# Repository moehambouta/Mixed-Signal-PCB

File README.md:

# Mixed Signal PCB Project

This repository contains all the source files for the Mixed Signal PCB Project, an endeavor to design and develop a PCB capable of signal generation and analysis within the audio band. The project is thoroughly documented through a series of blog posts available at [Mixed Signal PCB Project Blog](https://www.mohamedhambouta.com/article/36e01b97-5775-4c1d-bf0c-83d208441204).

## Repository Structure

- `Assembly` - Contains the bill of materials and assembly information.
- `Components` - Individual component files used in the design.
- `Gerber` - Gerber files necessary for PCB manufacturing.
- `Media` - Images and videos showcasing the PCB and its design process.
- `PCB` - The KiCAD PCB design file.
- `Schematics` - Schematic files for each section of the PCB design.

## Acknowledgments

Special thanks to Phil's Lab for their course, which significantly contributed to the knowledge and techniques applied in this project. Find the course details [here](https://phils-lab-shop.fedevel.education/itemDetail.html?itemtype=course&dbid=1606477016678&instrid=us-east-2_Vw1KnTvTs:107c257d-31cc-430a-95d7-3c5d70c578e0).

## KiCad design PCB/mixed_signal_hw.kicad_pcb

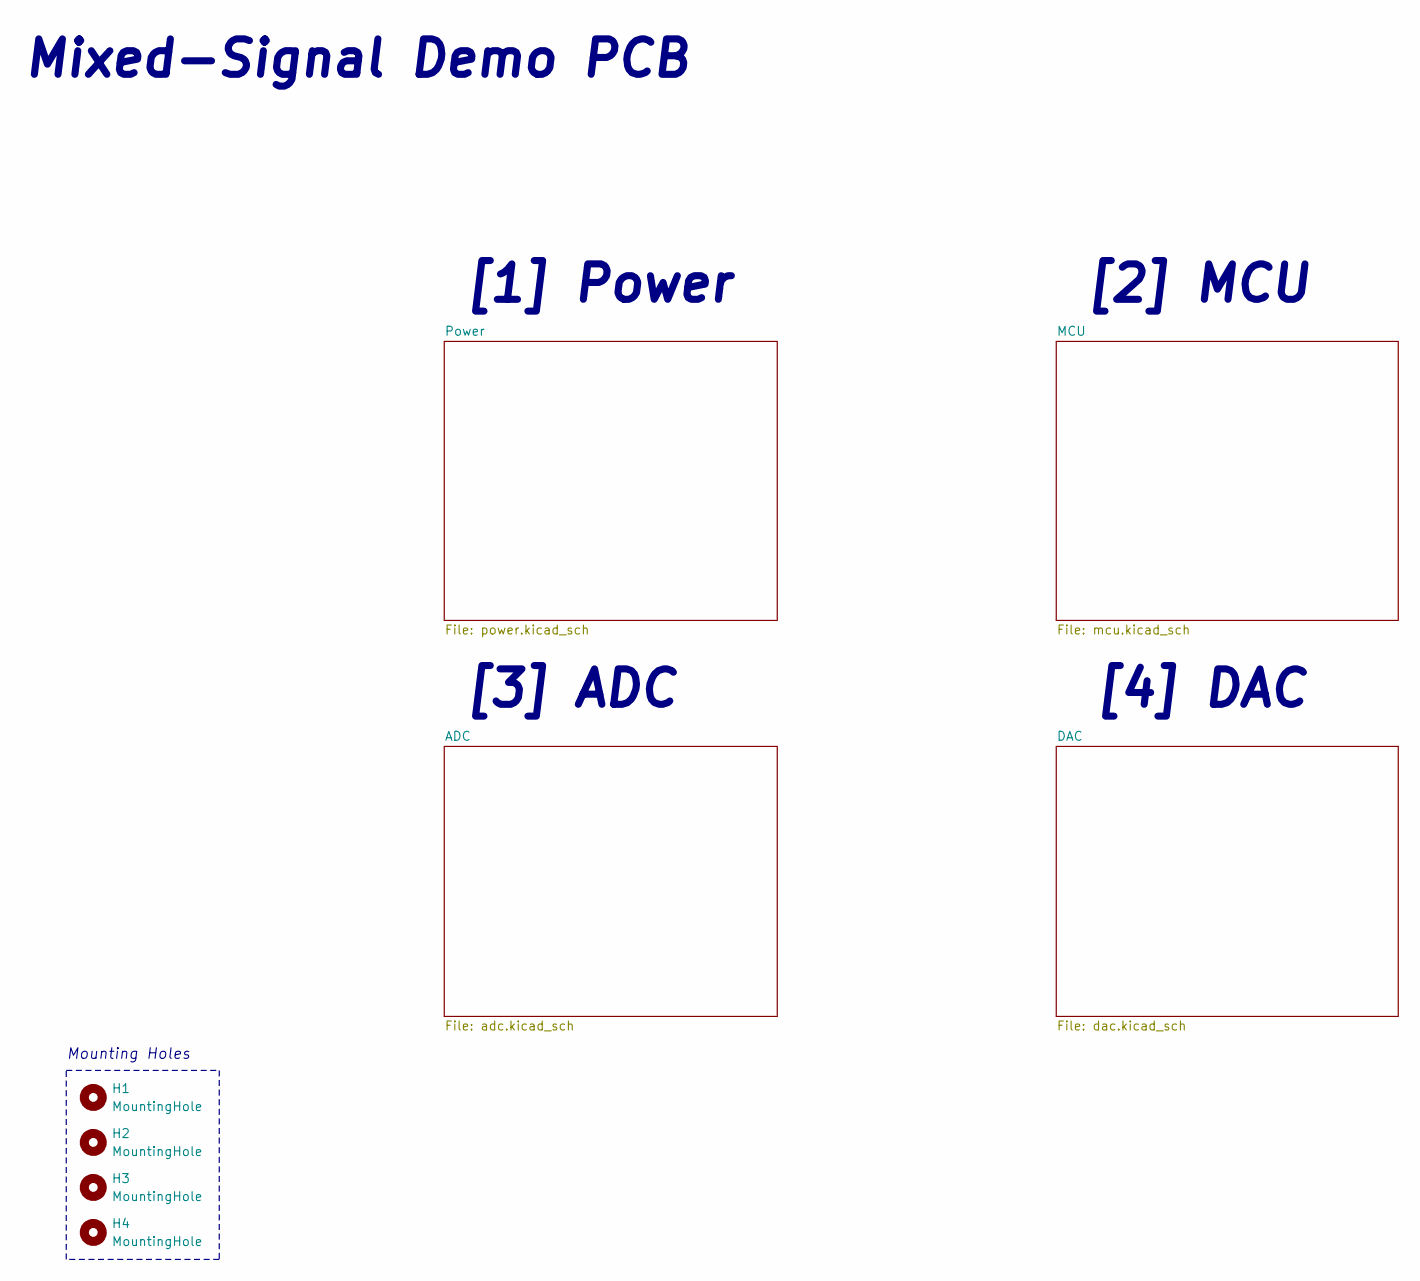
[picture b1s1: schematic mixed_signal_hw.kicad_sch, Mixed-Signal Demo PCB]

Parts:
H1, H2, H3, H4: MountingHole; MountingHole_3.2mm_M3

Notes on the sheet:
Mounting Holes
[4] DAC
[1] Power
[3] ADC
[2] MCU
Mixed-Signal Demo PCB

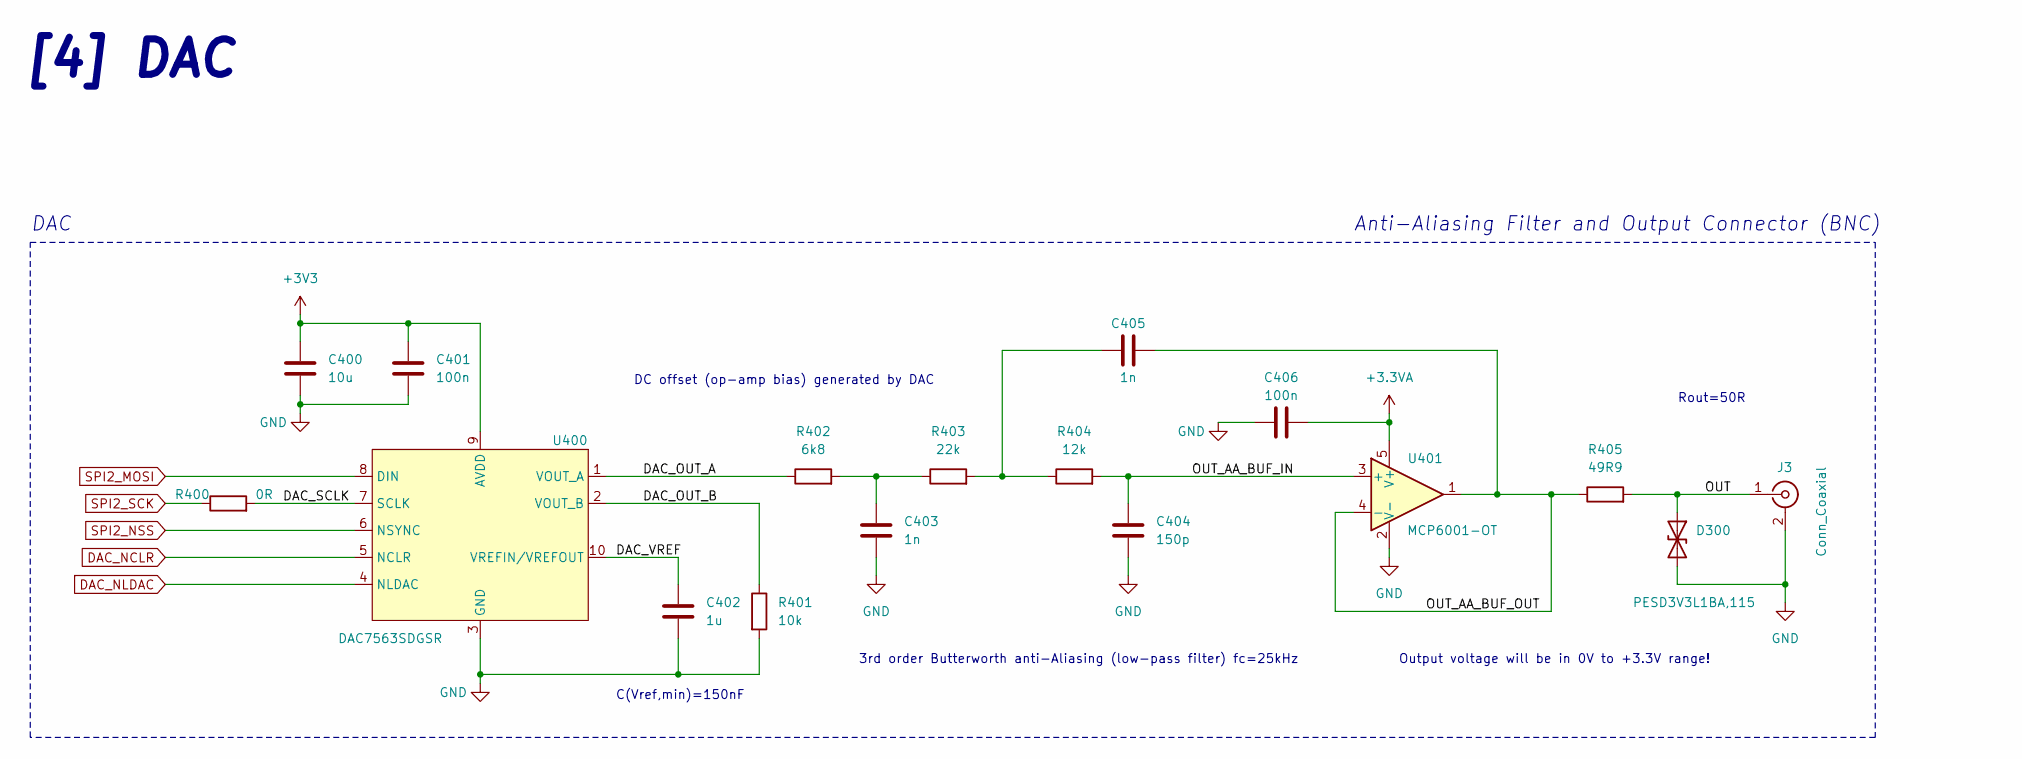
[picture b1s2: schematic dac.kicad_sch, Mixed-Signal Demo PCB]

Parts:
C400: 10u; C_0603_1608Metric
C401, C406: 100n; C_0402_1005Metric
C402: 1u; C_0603_1608Metric
C403, C405: 1n; C_0402_1005Metric
C404: 150p; C_0402_1005Metric
D300: PESD3V3L1BA,115; D_SOD-323
J3: Conn_Coaxial; AMPHENOL-BNC-031-5640-1010
R400: 0R; R_0402_1005Metric
R401: 10k; R_0402_1005Metric
R402: 6k8; R_0402_1005Metric
R403: 22k; R_0402_1005Metric
R404: 12k; R_0402_1005Metric
R405: 49R9; R_0402_1005Metric
U400: DAC7563SDGSR; VSSOP-10
U401: MCP6001-OT; SOT-23-5

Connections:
+3.3VA: C406.2, U401.5 (V+); also elsewhere on the board
+3V3: C400.1, C401.1, U400.9 (AVDD); also elsewhere on the board
/DAC/DAC_OUT_A: R402.1, U400.1 (VOUT_A)
/DAC/DAC_OUT_B: R401.1, U400.2 (VOUT_B)
/DAC/DAC_SCLK: R400.2, U400.7 (SCLK)
/DAC/DAC_VREF: C402.1, U400.10 (VREFIN/VREFOUT)
/DAC/OUT_AA_BUF_IN: C404.1, R404.2, U401.3 (+)
/DAC/OUT_AA_BUF_OUT: C405.2, R405.1, U401.1, U401.4 (-)
DAC_NCLR: U400.5 (NCLR); also elsewhere on the board
DAC_NLDAC: U400.4 (NLDAC); also elsewhere on the board
unnamed: C403.1, R402.2, R403.1
unnamed: C405.1, R403.2, R404.1
SPI2_MOSI: U400.8 (DIN); also elsewhere on the board
SPI2_NSS: U400.6 (NSYNC); also elsewhere on the board
SPI2_SCK: R400.1; also elsewhere on the board

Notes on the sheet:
Output voltage will be in 0V to +3.3V range!
Anti-Aliasing Filter and Output Connector (BNC)
3rd order Butterworth anti-Aliasing (low-pass filter) fc=25kHz
DAC
C(Vref,min)=150nF
DC offset (op-amp bias) generated by DAC
[4] DAC
Rout=50R

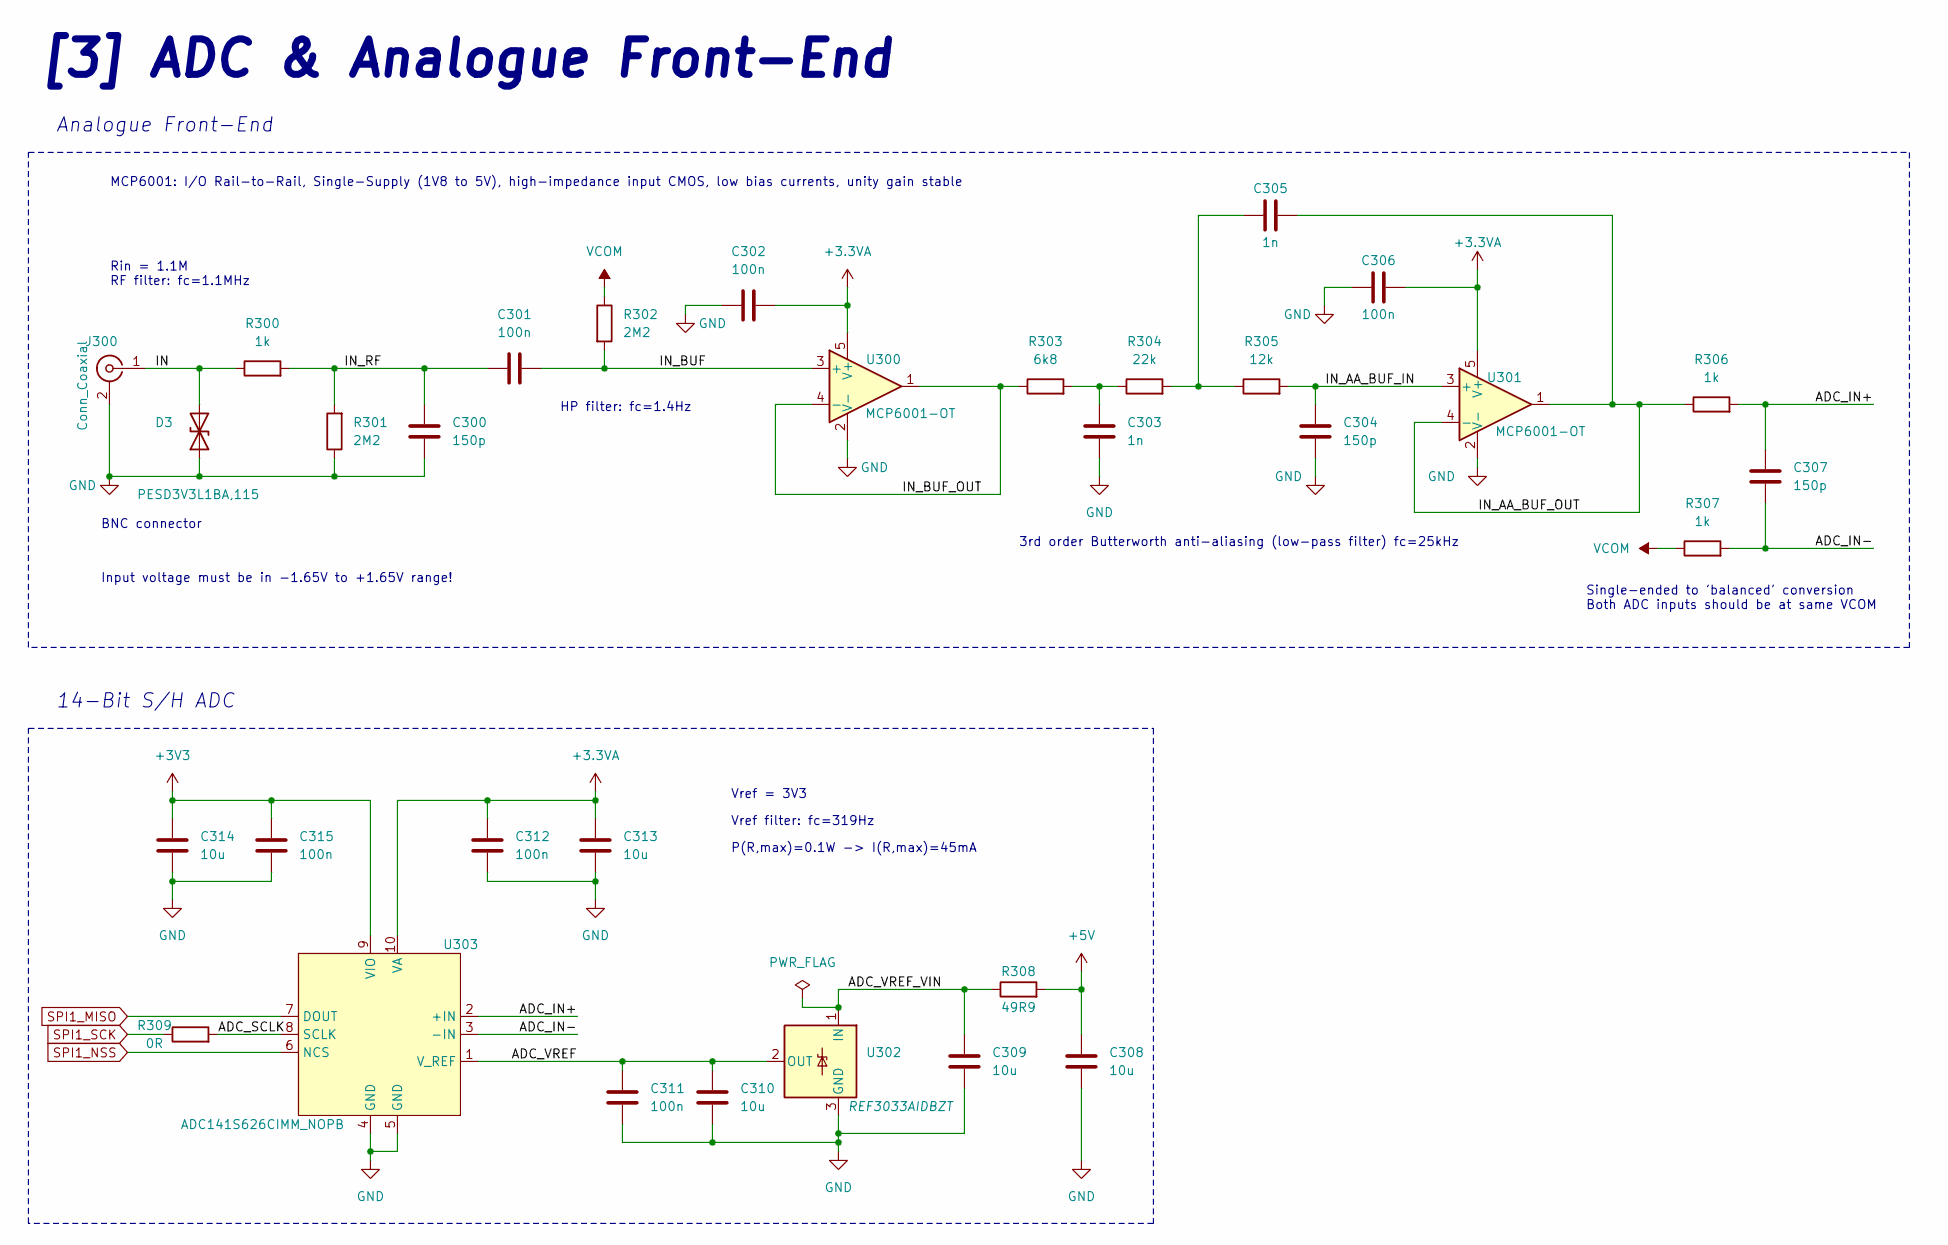
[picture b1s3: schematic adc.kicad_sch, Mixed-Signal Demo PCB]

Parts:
C300, C304, C307: 150p; C_0402_1005Metric
C301, C302, C306, C312, C315: 100n; C_0402_1005Metric
C303, C305: 1n; C_0402_1005Metric
C308, C309, C313, C314: 10u; C_0603_1608Metric
C310: 10u; C_0402_1005Metric
C311: 100n; C_0603_1608Metric
D3: PESD3V3L1BA,115; D_SOD-323
J300: Conn_Coaxial; AMPHENOL-BNC-031-5640-1010
R300, R306, R307: 1k; R_0402_1005Metric
R301, R302: 2M2; R_0402_1005Metric
R303: 6k8; R_0402_1005Metric
R304: 22k; R_0402_1005Metric
R305: 12k; R_0402_1005Metric
R308: 49R9; R_0402_1005Metric
R309: 0R; R_0402_1005Metric
U300, U301: MCP6001-OT; SOT-23-5
U302: REF3033AIDBZT; SOT-23
U303: ADC141S626CIMM_NOPB; VSSOP-10

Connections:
+3.3VA: C302.2, C306.1, C312.1, C313.1, U300.5 (V+), U301.5 (V+), U303.10 (VA); also elsewhere on the board
+3V3: C314.1, C315.1, U303.9 (VIO); also elsewhere on the board
+5V: C308.1, R308.2; also elsewhere on the board
/ADC/ADC_IN+: C307.1, R306.2, U303.2 (+IN)
/ADC/ADC_IN-: C307.2, R307.2, U303.3 (-IN)
/ADC/ADC_SCLK: R309.2, U303.8 (SCLK)
/ADC/ADC_VREF: C310.1, C311.1, U302.2 (OUT), U303.1 (V_REF)
/ADC/ADC_VREF_VIN: C309.1, R308.1, U302.1 (IN)
/ADC/IN_AA_BUF_IN: C304.1, R305.2, U301.3 (+)
/ADC/IN_AA_BUF_OUT: C305.1, R306.1, U301.1, U301.4 (-)
/ADC/IN_BUF: C301.2, R302.2, U300.3 (+)
/ADC/IN_BUF_OUT: R303.1, U300.1, U300.4 (-)
/ADC/IN_RF: C300.1, C301.1, R300.2, R301.2
unnamed: C303.1, R303.2, R304.1
unnamed: C305.2, R304.2, R305.1
SPI1_MISO: U303.7 (DOUT); also elsewhere on the board
SPI1_NSS: U303.6 (NCS); also elsewhere on the board
SPI1_SCK: R309.1; also elsewhere on the board
VCOM: R302.1, R307.1; also elsewhere on the board

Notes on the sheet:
HP filter: fc=1.4Hz
Single-ended to 'balanced' conversion Both ADC inputs should be at same VCOM
Vref filter: fc=319Hz
Rin = 1.1M RF filter: fc=1.1MHz
Vref = 3V3
Input voltage must be in -1.65V to +1.65V range!
3rd order Butterworth anti-aliasing (low-pass filter) fc=25kHz
MCP6001: I/O Rail-to-Rail, Single-Supply (1V8 to 5V), high-impedance input CMOS, low bias currents, unity gain stable
Analogue Front-End
BNC connector
14-Bit S/H ADC
[3] ADC & Analogue Front-End
P(R,max)=0.1W -> I(R,max)=45mA

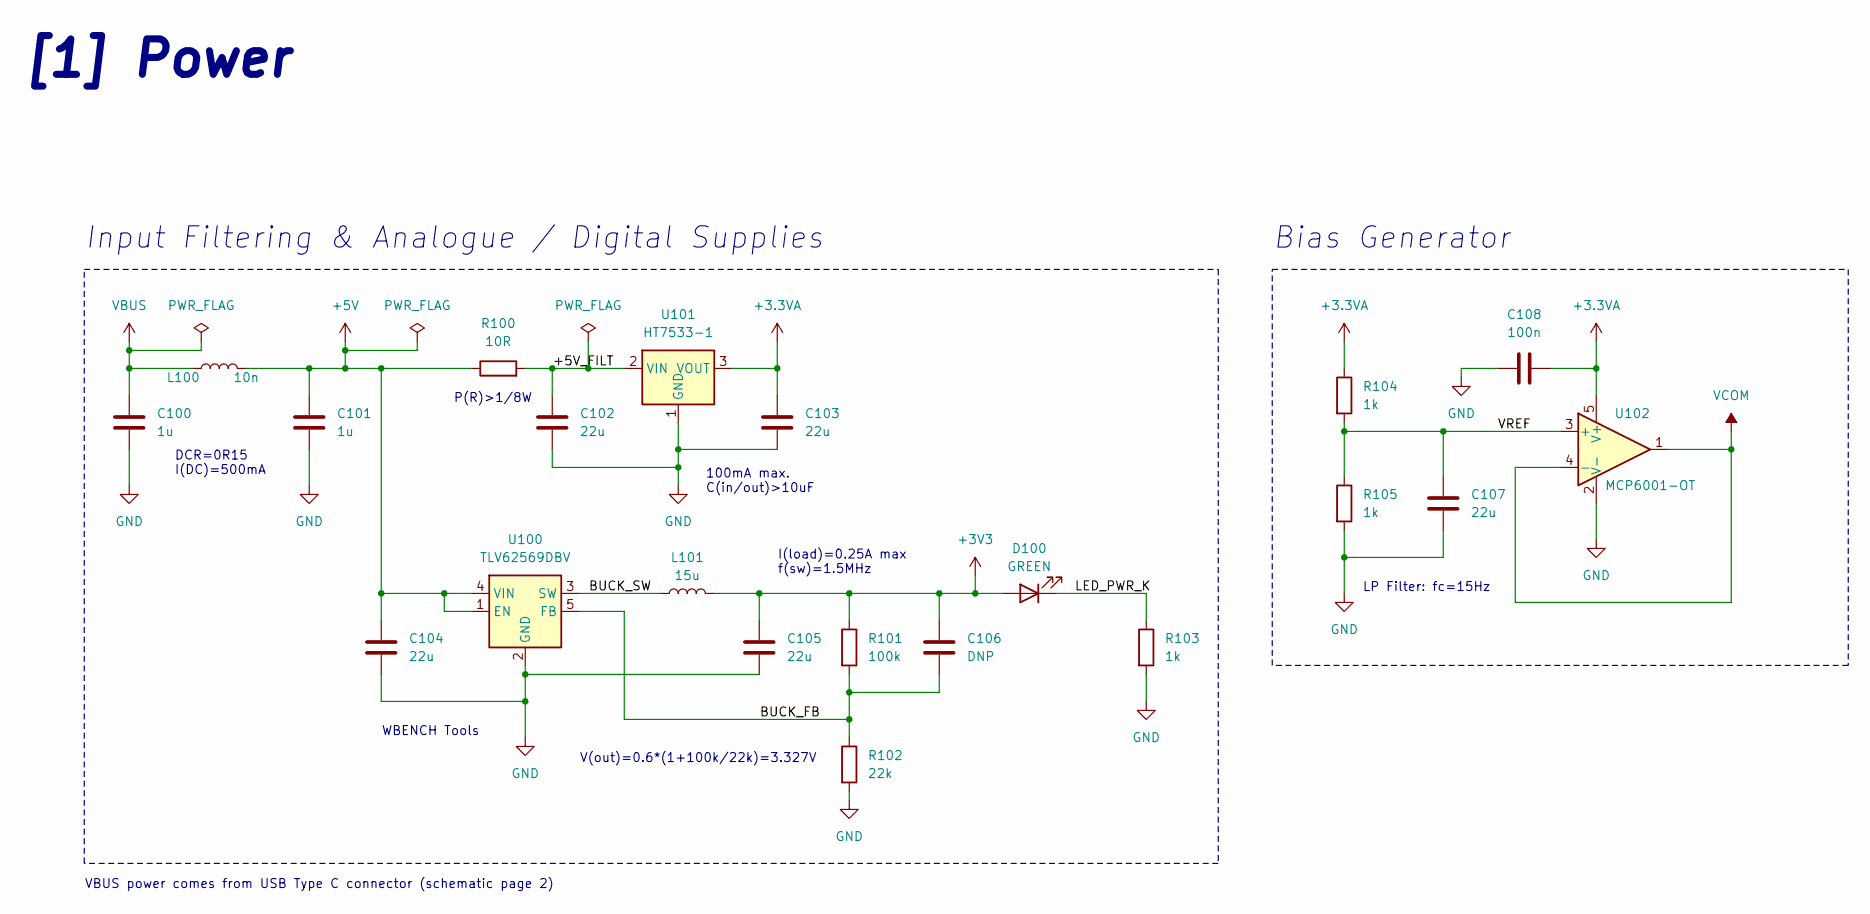
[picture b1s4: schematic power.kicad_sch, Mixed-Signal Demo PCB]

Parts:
C100, C101: 1u; C_0603_1608Metric
C102, C103, C104, C105, C107: 22u; C_0805_2012Metric
C106: DNP; C_0402_1005Metric
C108: 100n; C_0402_1005Metric
D100: GREEN; LED_0603_1608Metric
L100: 10n; L_0402_1005Metric
L101: 15u; MWSA0603S
R100: 10R; R_0805_2012Metric
R101: 100k; R_0402_1005Metric
R102: 22k; R_0402_1005Metric
R103, R104, R105: 1k; R_0402_1005Metric
U100: TLV62569DBV; SOT-23-5
U101: HT7533-1; SOT-89-3
U102: MCP6001-OT; SOT-23-5

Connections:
+3.3VA: C103.1, C108.2, R104.1, U101.3 (VOUT), U102.5 (V+); also elsewhere on the board
+3V3: C105.1, C106.1, D100.2 (A), L101.2, R101.1; also elsewhere on the board
+5V: C101.1, C104.1, L100.2, R100.1, U100.1 (EN), U100.4 (VIN); also elsewhere on the board
/Power/+5V_FILT: C102.1, R100.2, U101.2 (VIN)
/Power/BUCK_FB: C106.2, R101.2, R102.1, U100.5 (FB)
/Power/BUCK_SW: L101.1, U100.3 (SW)
/Power/LED_PWR_K: D100.1 (K), R103.1
/Power/VREF: C107.1, R104.2, R105.1, U102.3 (+)
VBUS: C100.1, L100.1; also elsewhere on the board
VCOM: U102.1, U102.4 (-); also elsewhere on the board

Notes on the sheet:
P(R)>1/8W
LP Filter: fc=15Hz
Bias Generator
DCR=0R15 I(DC)=500mA
VBUS power comes from USB Type C connector (schematic page 2)
Input Filtering & Analogue / Digital Supplies
I(load)=0.25A max f(sw)=1.5MHz
[1] Power
V(out)=0.6*(1+100k/22k)=3.327V
WBENCH Tools
100mA max. C(in/out)>10uF

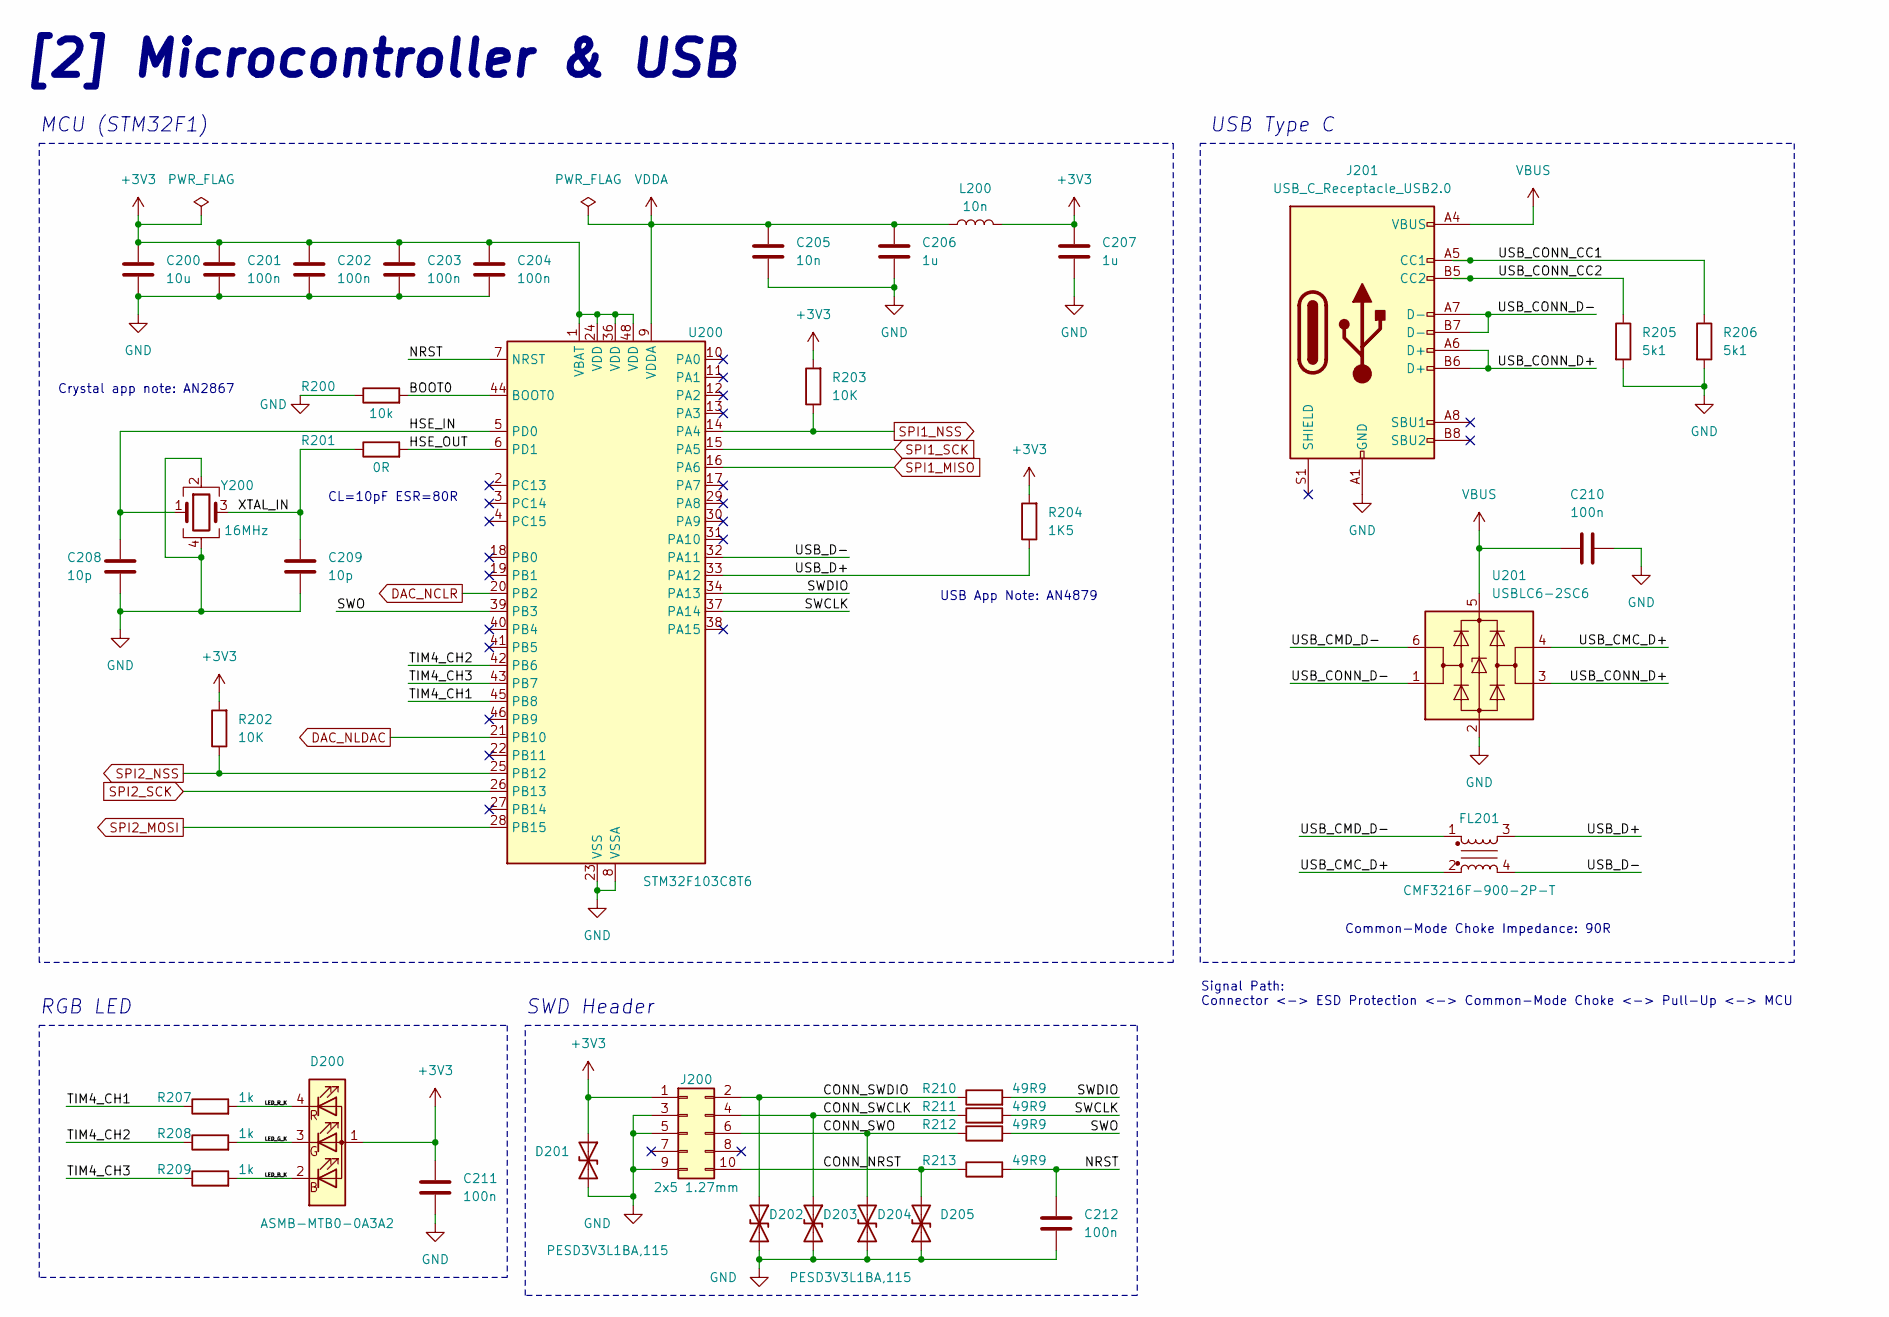
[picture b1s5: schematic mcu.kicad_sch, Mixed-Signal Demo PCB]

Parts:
C200: 10u; C_0603_1608Metric
C201, C202, C203, C204, C210, C211, C212: 100n; C_0402_1005Metric
C205: 10n; C_0402_1005Metric
C206, C207: 1u; C_0603_1608Metric
C208, C209: 10p; C_0402_1005Metric
D200: ASMB-MTB0-0A3A2; LED_Avago_PLCC4_3.2x2.8mm_CW
D201, D202, D203, D204, D205: PESD3V3L1BA,115; D_SOD-323
FL201: CMF3216F-900-2P-T; CMC-1206
J200: 2x5 1.27mm; PinHeader_2x05_P1.27mm_Vertical_SMD
J201: USB_C_Receptacle_USB2.0; USB_C_Receptacle_HRO_TYPE-C-31-M-12
L200: 10n; L_0402_1005Metric
R200: 10k; R_0402_1005Metric
R201: 0R; R_0402_1005Metric
R202, R203: 10K; R_0402_1005Metric
R204: 1K5; R_0402_1005Metric
R205, R206: 5k1; R_0402_1005Metric
R207, R208, R209: 1k; R_0402_1005Metric
R210, R211, R212, R213: 49R9; R_0402_1005Metric
U200: STM32F103C8T6; LQFP-48_7x7mm_P0.5mm
U201: USBLC6-2SC6; SOT-23-6
Y200: 16MHz; Crystal_SMD_3225-4Pin_3.2x2.5mm

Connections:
+3V3: C200.1, C201.1, C202.1, C203.1, C204.1, C207.1, C211.1, D200.1 (A), D201.1 (A1), J200.1, L200.2, R202.2, R203.2, R204.2, U200.1 (VBAT), U200.24 (VDD), U200.36 (VDD), U200.48 (VDD); also elsewhere on the board
/MCU/BOOT0: R200.2, U200.44 (BOOT0)
/MCU/CONN_NRST: D205.2 (A2), J200.10, R213.1
/MCU/CONN_SWCLK: D203.1 (A1), J200.4, R211.1
/MCU/CONN_SWDIO: D202.1 (A1), J200.2, R210.1
/MCU/CONN_SWO: D204.2 (A2), J200.6, R212.1
/MCU/HSE_IN: C208.1, U200.5 (PD0), Y200.1
/MCU/HSE_OUT: R201.2, U200.6 (PD1)
/MCU/LED_B_K: D200.2 (BK), R209.2
/MCU/LED_G_K: D200.3 (GK), R208.2
/MCU/LED_R_K: D200.4 (RK), R207.2
/MCU/NRST: C212.1, R213.2, U200.7 (NRST)
/MCU/SWCLK: R211.2, U200.37 (PA14)
/MCU/SWDIO: R210.2, U200.34 (PA13)
/MCU/SWO: R212.2, U200.39 (PB3)
/MCU/TIM4_CH1: R207.1, U200.45 (PB8)
/MCU/TIM4_CH2: R208.1, U200.42 (PB6)
/MCU/TIM4_CH3: R209.1, U200.43 (PB7)
/MCU/USB_CMC_D+: FL201.2, U201.4 (I/O2)
/MCU/USB_CMD_D-: FL201.1, U201.6 (I/O1)
/MCU/USB_CONN_CC1: J201.A5 (CC1), R206.1
/MCU/USB_CONN_CC2: J201.B5 (CC2), R205.1
/MCU/USB_CONN_D+: J201.A6 (D+), J201.B6 (D+), U201.3 (I/O2)
/MCU/USB_CONN_D-: J201.A7 (D-), J201.B7 (D-), U201.1 (I/O1)
/MCU/USB_D+: FL201.3, R204.1, U200.33 (PA12)
/MCU/USB_D-: FL201.4, U200.32 (PA11)
/MCU/XTAL_IN: C209.1, R201.1, Y200.3
DAC_NCLR: U200.20 (PB2); also elsewhere on the board
DAC_NLDAC: U200.21 (PB10); also elsewhere on the board
SPI1_MISO: U200.16 (PA6); also elsewhere on the board
SPI1_NSS: R203.1, U200.14 (PA4); also elsewhere on the board
SPI1_SCK: U200.15 (PA5); also elsewhere on the board
SPI2_MOSI: U200.28 (PB15); also elsewhere on the board
SPI2_NSS: R202.1, U200.25 (PB12); also elsewhere on the board
SPI2_SCK: U200.26 (PB13); also elsewhere on the board
VBUS: C210.1, J201.A4 (VBUS), J201.A9 (VBUS), J201.B4 (VBUS), J201.B9 (VBUS), U201.5 (VBUS); also elsewhere on the board
VDDA: C205.1, C206.1, L200.1, U200.9 (VDDA)

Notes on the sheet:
Common-Mode Choke Impedance: 90R
Crystal app note: AN2867
RGB LED
[2] Microcontroller & USB
USB App Note: AN4879
CL=10pF ESR=80R
MCU (STM32F1)
SWD Header
Signal Path: Connector <-> ESD Protection <-> Common-Mode Choke <-> Pull-Up <-> MCU
USB Type C

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
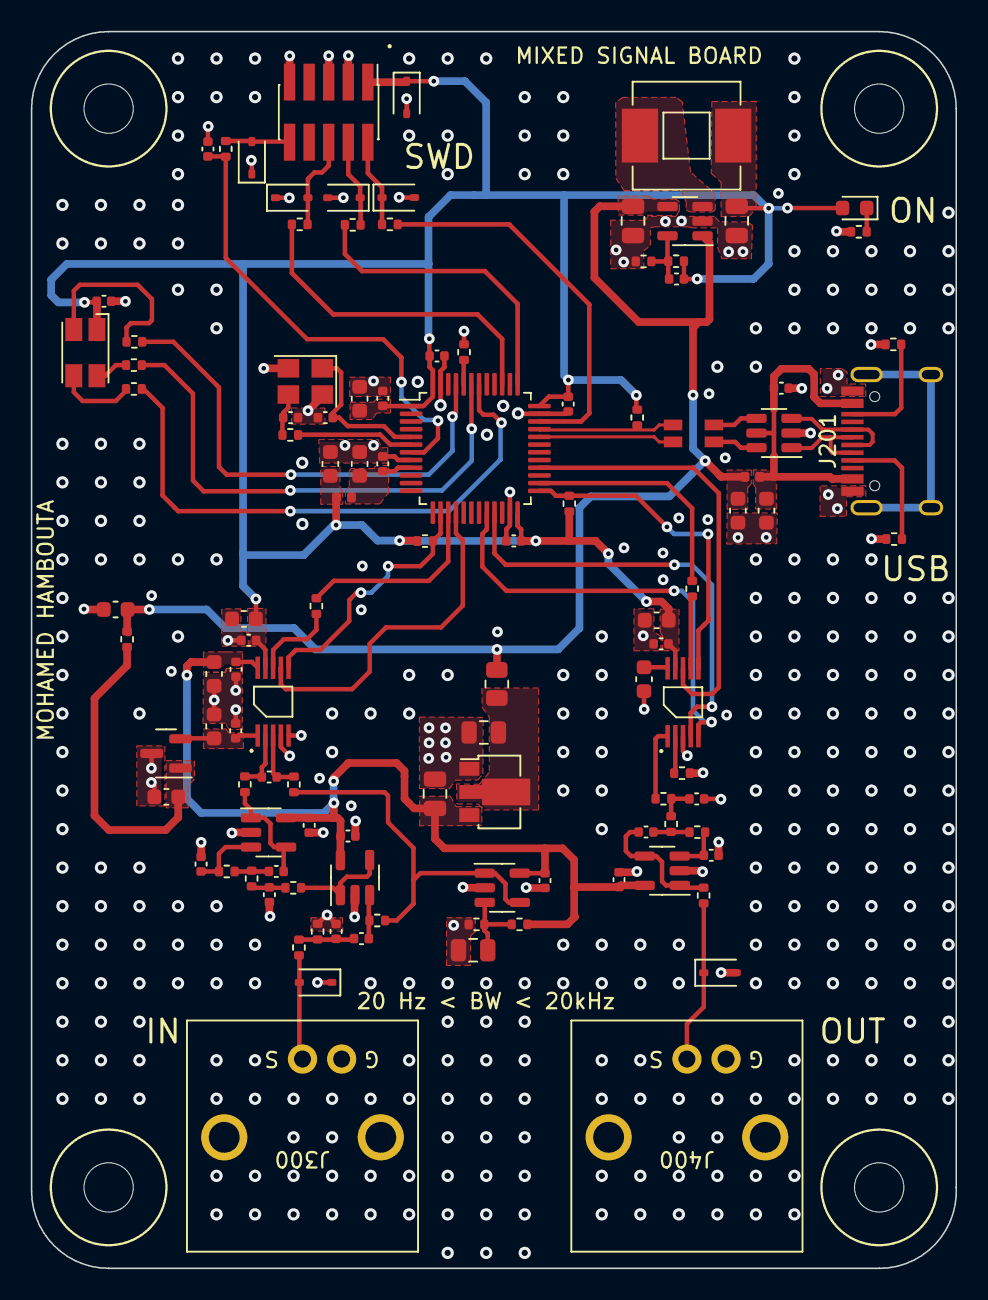
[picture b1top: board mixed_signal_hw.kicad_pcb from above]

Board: 4 copper layers, 60.0 x 80.3 mm, 114 parts (0 on the bottom side), 68 nets.

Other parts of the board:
D400: PESD3V3L1BA,115; D_SOD-323
J400: Conn_Coaxial; AMPHENOL-BNC-031-5640-1010

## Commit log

2024-01-02 Init
2024-01-02 Updated index.html
2024-01-03 Progress
2024-01-03 Updated images path to be compaitable with github pages
2024-01-03 Updated images and path for github pages
2024-01-03 minor frontend updates
2024-01-03 major frontend updates
2024-01-03 Updated src for video tag
2024-01-03 Improved image quality
2024-01-03 added simple mobile support
2024-01-03 upadted nav links
2024-01-03 minor text change
2024-01-08 restructuring repo
2024-01-08 frontend design improvements
2024-01-08 dynamic content feature
2024-01-08 fixed title in usb html
2024-01-09 inline pagination
2024-01-09 Updated introduction content
2024-01-09 updated blog content
2024-01-09 Added dsp images
2024-01-09 fixed page titles
2024-01-09 fixed next steps hyperlink
2024-01-09 Added source files
2024-01-09 Added README
2024-01-09 fixed image links
2024-01-10 fixed typo
2024-01-30 minor changes
2024-02-05 Updated content
